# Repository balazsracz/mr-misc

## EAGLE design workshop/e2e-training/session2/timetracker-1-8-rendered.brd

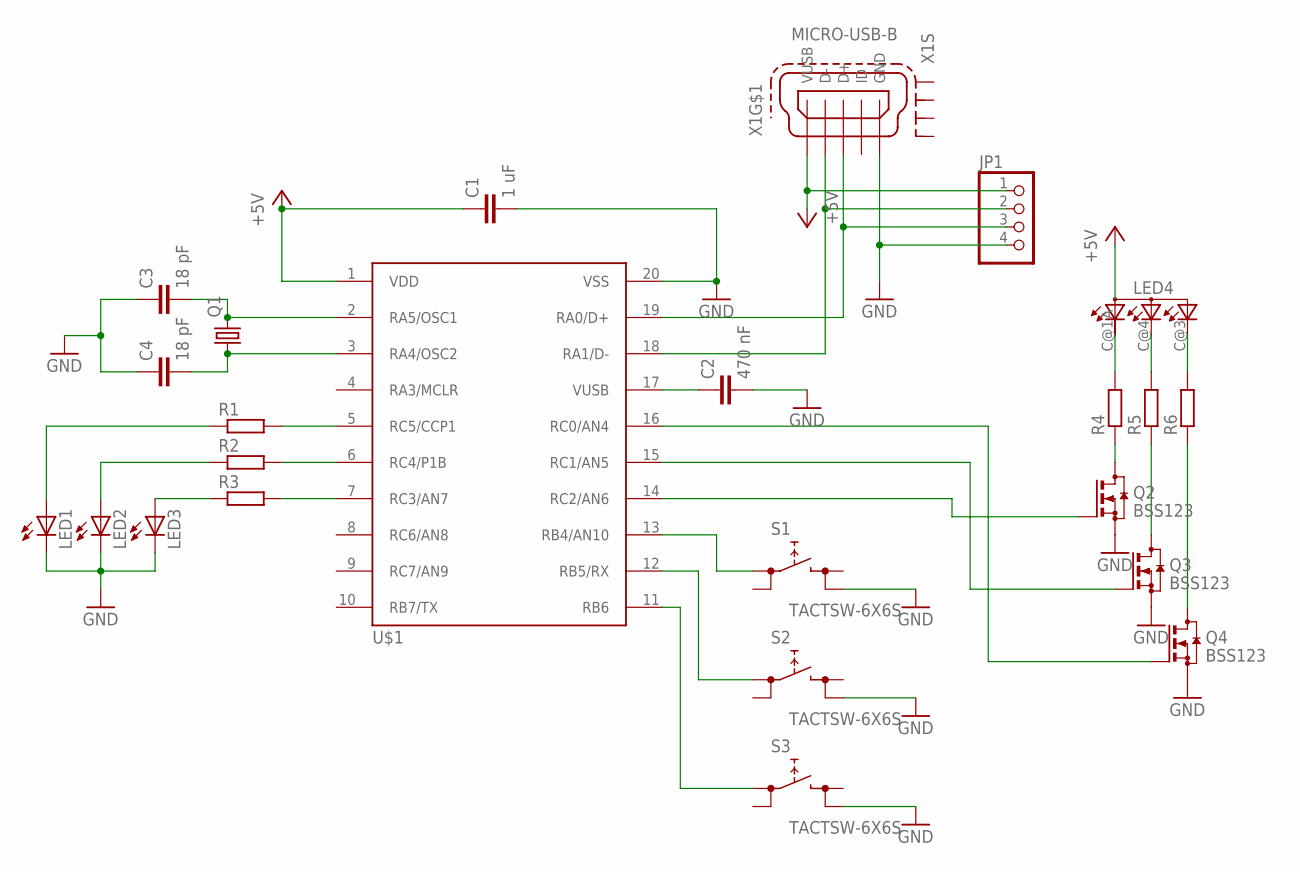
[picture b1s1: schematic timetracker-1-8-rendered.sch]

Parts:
C1: 1 uF; C0805
C2: 470 nF; C0805
C3, C4: 18 pF; C0805
JP1: PINHD-1X4; 1X04
LED1, LED2, LED3: LEDSML0805; SML0805
LED4: RGBLED-3P-LCC-4; P-LCC-4
Q1: CRYSTALHC49UP; HC49UP
Q2, Q3, Q4: BSS123; SOT23
R1, R2, R3, R4, R5, R6: R-EU_R0805; R0805
S1, S2, S3: TACTSW-6X6S; TACTSW-6X6
U$1: PIC18F14K50SMD; DIL20-SMD
X1: MICRO-USB-B; MICRO-B-PAC

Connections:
+5V: C1.1, JP1.1, LED4.A (A2), U$1.1 (VDD), X1.1 (VUSB)
GND: C1.2, C2.2, C3.1, C4.1, JP1.4, LED1.C, LED2.C, LED3.C, Q2.2 (S), Q3.2 (S), Q4.2 (S), S1.4 (2.2), S2.4 (2.2), S3.4 (2.2), U$1.20 (VSS), X1.5 (GND)
unnamed: JP1.3, U$1.19 (RA0/D+), X1.3 (D+)
unnamed: C3.2, Q1.2, U$1.2 (RA5/OSC1)
unnamed: C2.1, U$1.17 (VUSB)
unnamed: C4.2, Q1.1, U$1.3 (RA4/OSC2)
unnamed: JP1.2, U$1.18 (RA1/D-), X1.2 (D-)
unnamed: R3.2, U$1.7 (RC3/AN7)
unnamed: R2.2, U$1.6 (RC4/P1B)
unnamed: R1.2, U$1.5 (RC5/CCP1)
unnamed: LED1.A, R1.1
unnamed: LED2.A, R2.1
unnamed: LED3.A, R3.1
unnamed: LED4.C@1 (CRED), R4.2
unnamed: LED4.C@4 (CGREEN), R5.2
unnamed: S1.1 (1.1), U$1.13 (RB4/AN10)
unnamed: S2.1 (1.1), U$1.12 (RB5/RX)
unnamed: LED4.C@3 (CBLUE), R6.2
unnamed: Q2.3 (D), R4.1
unnamed: Q3.3 (D), R5.1
unnamed: Q4.3 (D), R6.1
unnamed: Q4.1 (G), U$1.16 (RC0/AN4)
unnamed: Q3.1 (G), U$1.15 (RC1/AN5)
unnamed: Q2.1 (G), U$1.14 (RC2/AN6)
unnamed: S3.1 (1.1), U$1.11 (RB6)

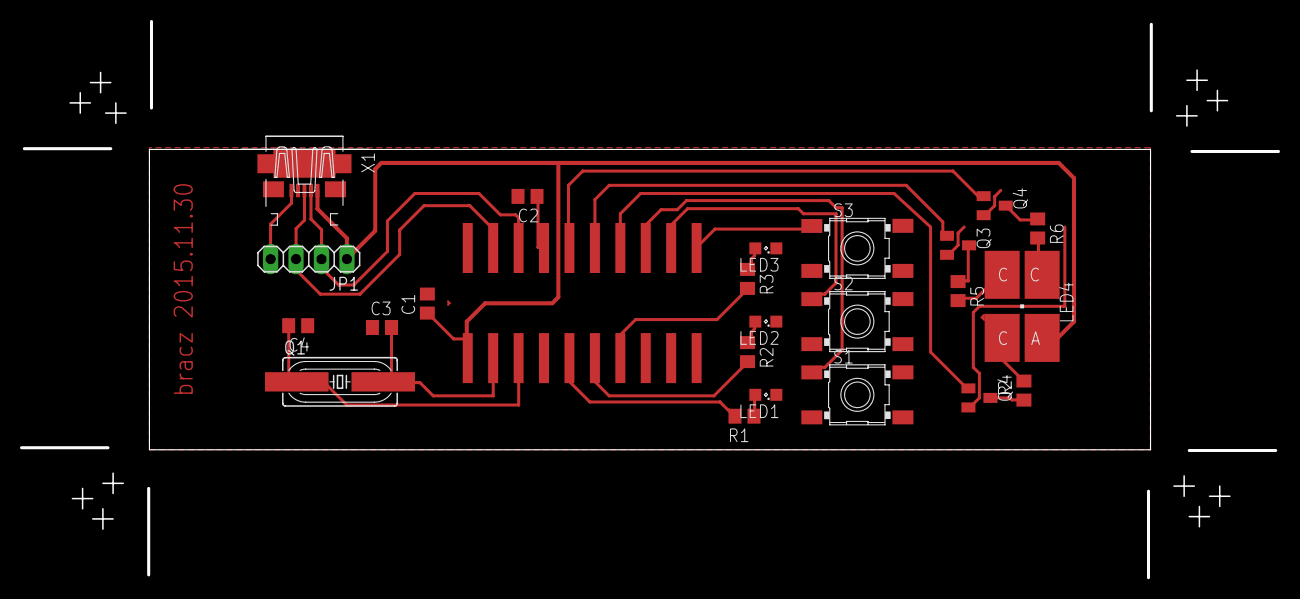
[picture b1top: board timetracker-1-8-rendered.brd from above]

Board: 2 copper layers, 100.0 x 30.0 mm, 24 parts (0 on the bottom side), 25 nets.
